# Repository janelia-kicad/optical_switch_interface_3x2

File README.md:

# optical_switch_interface_3x2

Authors:

    Peter Polidoro <polidorop@janelia.hhmi.org>

License:

    BSD

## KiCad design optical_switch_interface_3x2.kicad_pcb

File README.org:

#+TITLE: optical_switch_interface_3x2
#+AUTHOR: Peter Polidoro
#+EMAIL: peter@polidoro.io

* Repository Information
  - Author :: Peter Polidoro
  - License :: Open-Source Hardware

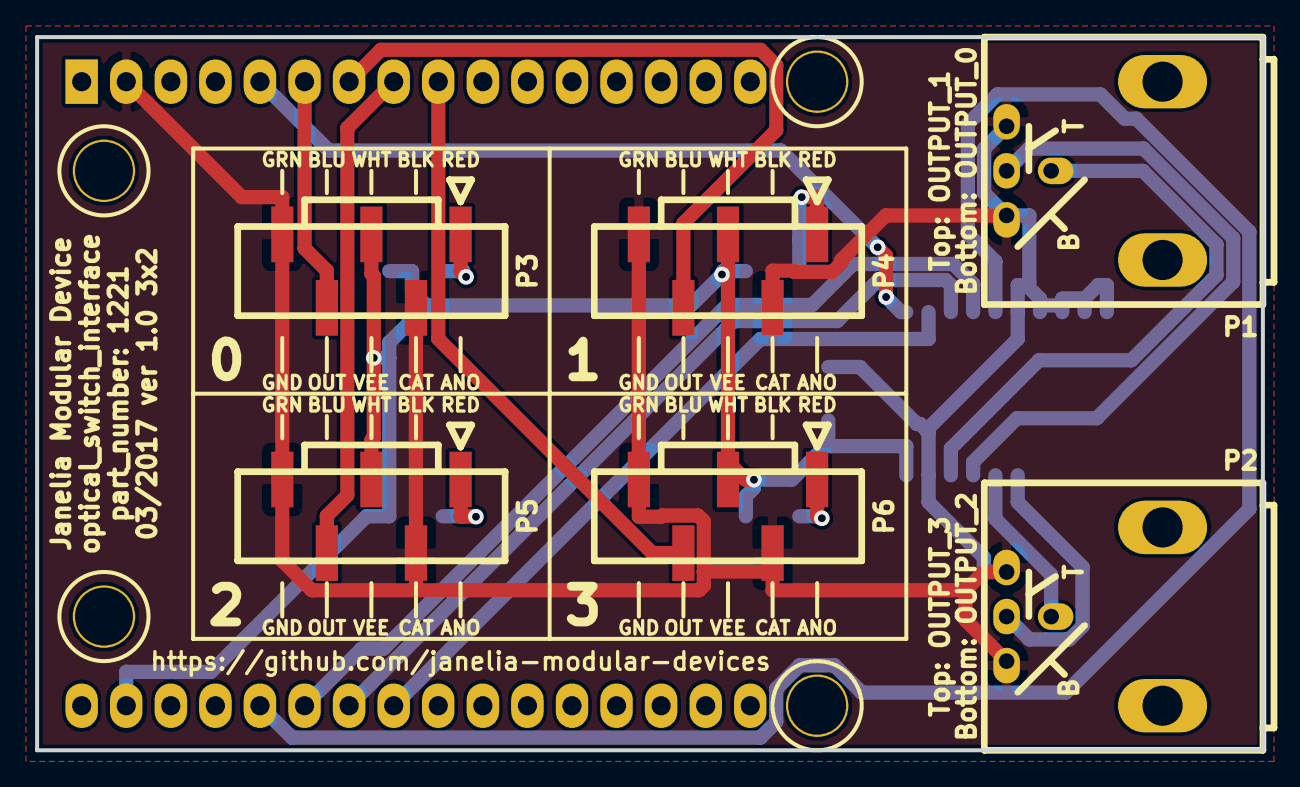
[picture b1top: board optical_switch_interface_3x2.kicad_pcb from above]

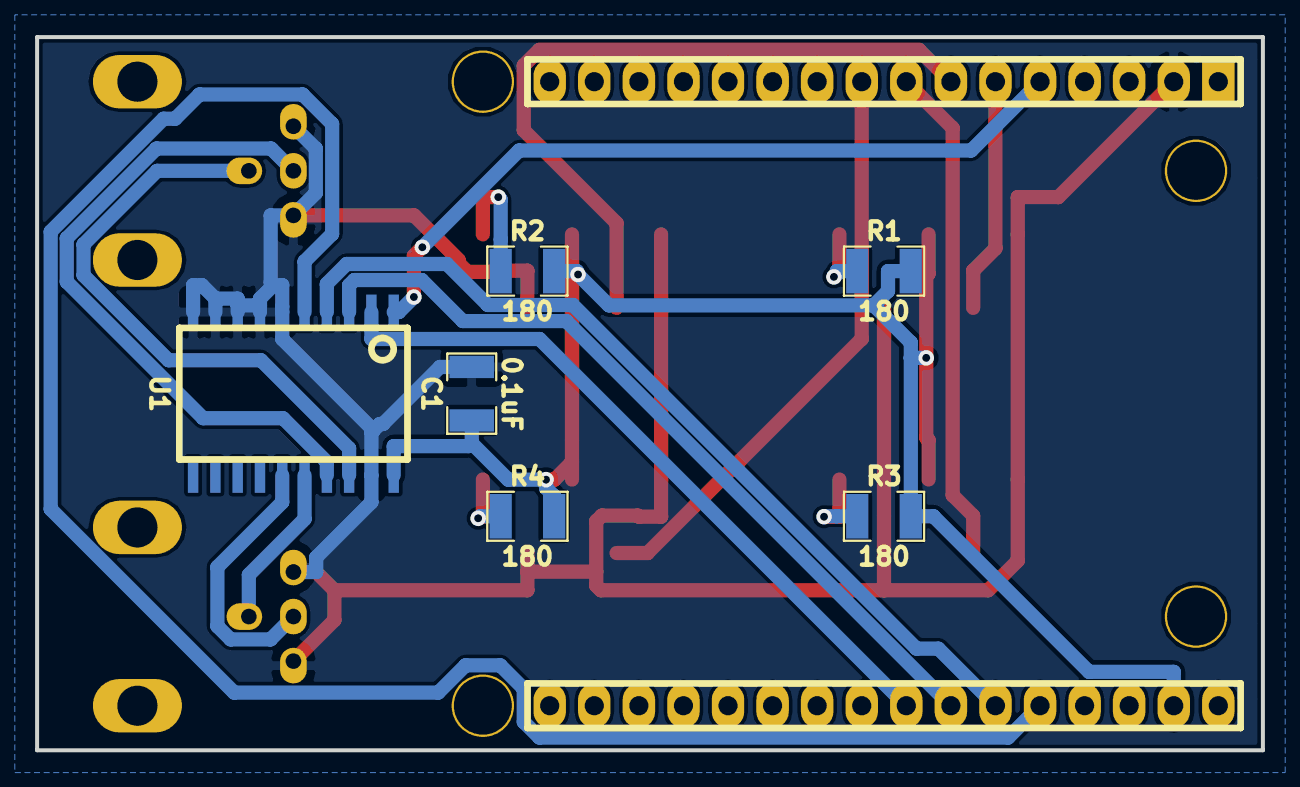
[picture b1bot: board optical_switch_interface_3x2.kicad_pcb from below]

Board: 2 copper layers, 69.8 x 40.6 mm, 13 parts (6 on the bottom side), 19 nets.

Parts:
C1: 0.1uF; SM1210
MDB1: MODULAR_DEVICE_BASE_3X2_MALE
P1, P2: BNC_DOUBLE_RA; BNC_DOUBLE
P3, P4, P5, P6: HEADER_01X05_SMD_SHR; Header_Shrouded_5_Pin_SMD
R1, R2, R3, R4: 180; SM1210
U1: SN74ABT541BDWR; SOIC_20

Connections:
/IN_0: MDB1.3, P3.4
/IN_1: MDB1.4, P4.4
/IN_2: MDB1.5, P5.4
/IN_3: MDB1.6, P6.4
/OUTPUT_0: P1.1, U1.18
/OUTPUT_1: P1.3, U1.17
/OUTPUT_2: P2.1, U1.16
/OUTPUT_3: P2.3, U1.15
/OUT_0: MDB1.20, U1.2
/OUT_1: MDB1.21, U1.3
/OUT_2: MDB1.22, U1.4
/OUT_3: MDB1.23, U1.5
/~ENABLE: MDB1.2, U1.1
GND: C1.2, MDB1.GND, P1.2, P1.4, P2.2, P2.4, P3.2, P3.5, P4.2, P4.5, P5.2, P5.5, P6.2, P6.5, U1.6, U1.7, U1.8, U1.9, U1.10, U1.19
unnamed: P3.1, R1.1
unnamed: P4.1, R2.1
unnamed: P5.1, R3.1
unnamed: P6.1, R4.1
VEE: C1.1, MDB1.VEE, P3.3, P4.3, P5.3, P6.3, R1.2, R2.2, R3.2, R4.2, U1.20

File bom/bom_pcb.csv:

Item,Reference(s),Value,Quantity,Description,PartNumber,Vendor
1,C1,0.1uF,1,CAP CER 0.1UF 50V 10% X7R 1210,478-3586-1-ND,digikey
2,MDB1,MODULAR_DEVICE_BASE_3X2_MALE,2,16 Position Header Through Hole Male Pins,S1011E-16-ND,digikey
3,P1 P2,BNC_DOUBLE_RA,2,CONN BNC JACK R/A 75 OHM PCB,ACX1655-ND,digikey
4,P3 P4 P5 P6,HEADER_01X05_SMD_SHR,4,CONN HEADER .100 VERT 5POS SMD,WM7205-ND,digikey
5,R1 R2 R3 R4,180,4,RES SMD 180 OHM 5% 1/2W 1210,P180VCT-ND,digikey
6,U1,SN74ABT541BDWR,1,Buffer Non-Inverting 1 Element 8 Bit per Element Push-Pull Output 20-SOIC,296-14668-1-ND,digikey

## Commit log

2017-03-08 Initial commit.
2017-03-08 Added components and footprints.
2017-03-08 Finished version 1.0.
2017-03-08 Added BNC cables to bom.
2017-03-24 Updated documentation.
2017-06-15 Removed .cmp file.
2017-09-13 Updated 0.1uF capacitors.
2017-09-22 Removed extra libraries.
2018-01-08 Updated to v4.
2018-01-08 Added v4 files.
2018-01-08 Updated gitignore.
2018-03-09 Update license from software to hardware.
2018-04-12 README.md -> README.org.
2018-04-19 Added .DS_Store to .gitignore.
2018-05-16 Added generate_kicad_documentation submodule.
2018-05-17 Updated submodules.
2018-08-12 Marked extra Teensy pins.
2018-08-12 Removed v4 files.
2018-08-24 Removed F.SilkS from pads.
2021-09-16 Update email address
2021-09-21 Remove ignored files
2022-02-22 Add guix files
2022-02-23 Add guix documentation
